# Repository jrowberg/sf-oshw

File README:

This repository holds various design files for hardware developed for SectorFej products and projects, such as the Bluegiga WT12 breakout boards.

For modules that have multiple versions published, it is usually desirable to use the most recent version unless you have a very specific reason not to. Duh, I know.

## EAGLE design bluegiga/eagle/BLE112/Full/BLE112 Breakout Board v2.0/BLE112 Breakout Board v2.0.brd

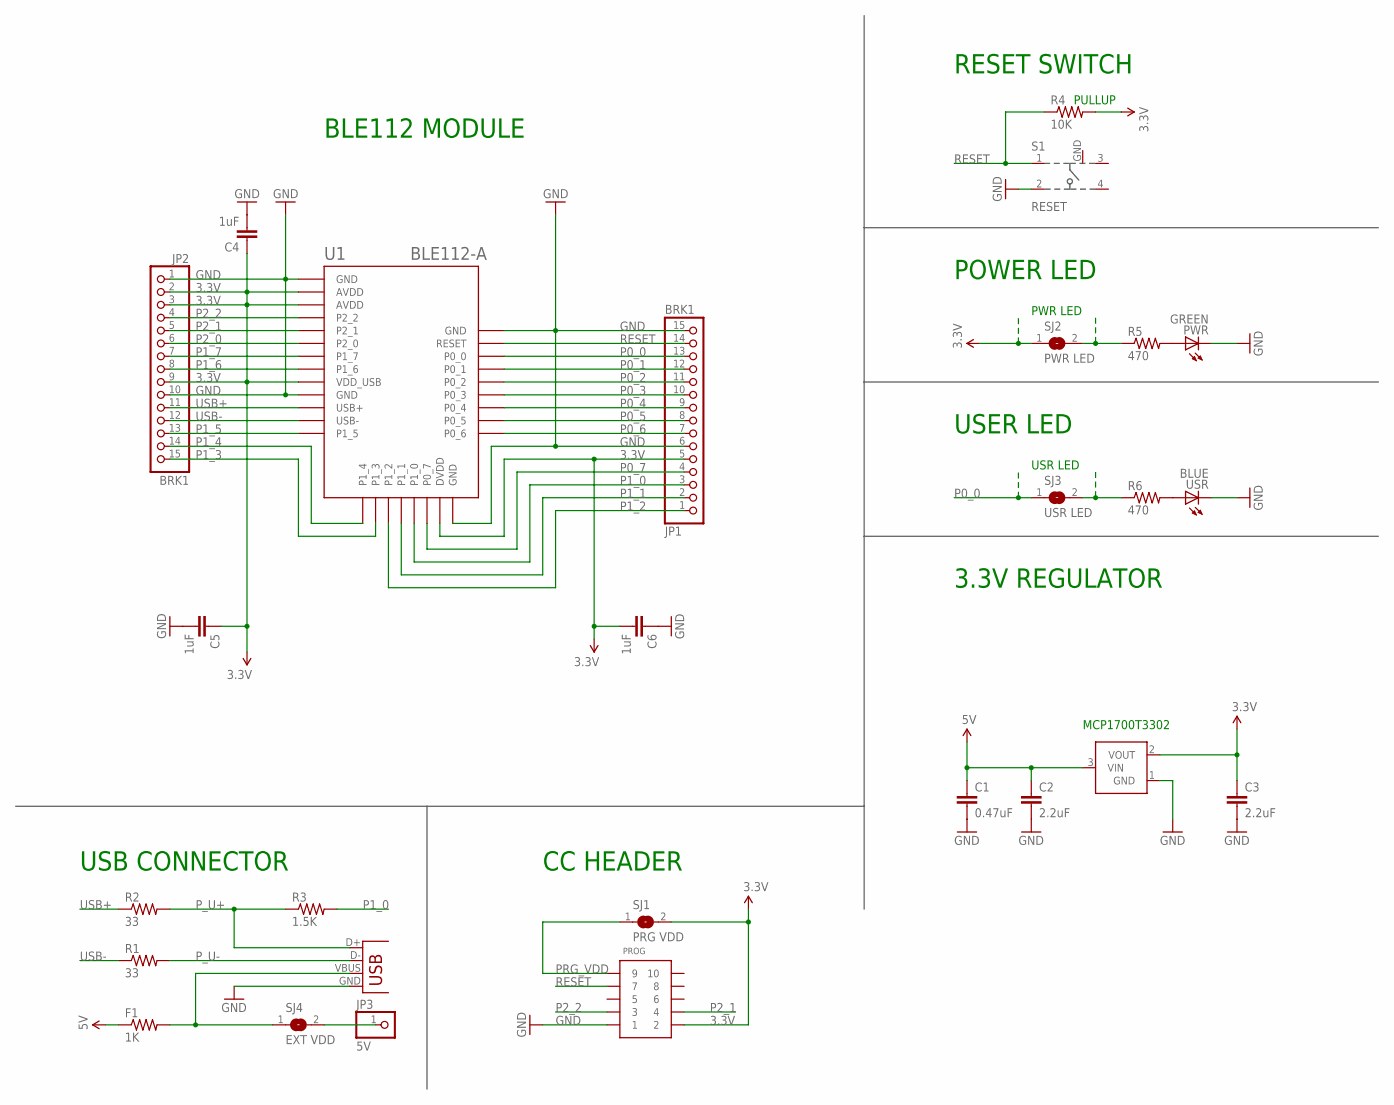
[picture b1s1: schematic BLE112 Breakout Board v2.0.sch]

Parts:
C1: 0.47uF; 0603-CAP
C2, C3: 2.2uF; 0603-CAP
C4, C5, C6: 1uF; 0603-CAP
F1: 1K; 0805
JP1, JP2: BRK1; 1X15
JP3: 5V; 1X01
PROG: CONN_5-2-FTSH-V; FTSH-105-DV
PWR: GREEN; CHIPLED_0805
R1, R2: 33; 0603-RES
R3: 1.5K; 0603-RES
R4: 10K; 0603-RES
R5, R6: 470; R0603
S1: RESET; 101-IG
SJ1: PRG VDD; SJ
SJ2: PWR LED; SJ
SJ3: USR LED; SJ
SJ4: EXT VDD; SJ
U1: BLE112-A
U2: MCP1700; SOT23-3
USB: USB-MICROB
USR: BLUE; CHIPLED_0805

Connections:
3.3V: C3.1, C4.1, C5.1, C6.2, JP1.5, JP2.2, JP2.3, JP2.9, PROG.2, R4.2, SJ1.2, SJ2.1, U1.AVDD1 (AVDD), U1.AVDD2 (AVDD), U1.DVDD, U1.VDD_USB, U2.2 (VOUT)
5V: C1.1, C2.1, F1.1, U2.3 (VIN)
GND: C1.2, C2.2, C3.2, C4.2, C5.2, C6.1, JP1.6, JP1.15, JP2.1, JP2.10, PROG.1, PWR.C, S1.2, S1.GND, U1.GND1 (GND), U1.GND2 (GND), U1.GND3 (GND), U1.GND4 (GND), U2.1 (GND), USB.GND, USR.C
unnamed: PWR.A, R5.2
unnamed: R5.1, SJ2.2
unnamed: R6.2, USR.A
unnamed: R6.1, SJ3.2
unnamed: JP3.1, SJ4.2
P0_0: JP1.13, SJ3.1, U1.P0_0
P0_1: JP1.12, U1.P0_1
P0_2: JP1.11, U1.P0_2
P0_3: JP1.10, U1.P0_3
P0_4: JP1.9, U1.P0_4
P0_5: JP1.8, U1.P0_5
P0_6: JP1.7, U1.P0_6
P0_7: JP1.4, U1.P0_7
P1_0: JP1.3, R3.2, U1.P1_0
P1_1: JP1.2, U1.P1_1
P1_2: JP1.1, U1.P1_2
P1_3: JP2.15, U1.P1_3
P1_4: JP2.14, U1.P1_4
P1_5: JP2.13, U1.P1_5
P1_6: JP2.8, U1.P1_6
P1_7: JP2.7, U1.P1_7
P2_0: JP2.6, U1.P2_0
P2_1: JP2.5, PROG.4, U1.P2_1
P2_2: JP2.4, PROG.3, U1.P2_2
PRG_VDD: PROG.9, SJ1.1
P_U+: R2.2, R3.1, USB.D+
P_U-: R1.2, USB.D-
RESET: JP1.14, PROG.7, R4.1, S1.1, U1.RESET
USB+: JP2.11, R2.1, U1.USB+
USB-: JP2.12, R1.1, U1.USB-
VBUS: F1.2, SJ4.1, USB.VBUS

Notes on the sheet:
PWR LED
USR LED
POWER LED
USER LED
USB CONNECTOR
CC HEADER
BLE112 MODULE
3.3V REGULATOR
RESET SWITCH
PULLUP
MCP1700T3302

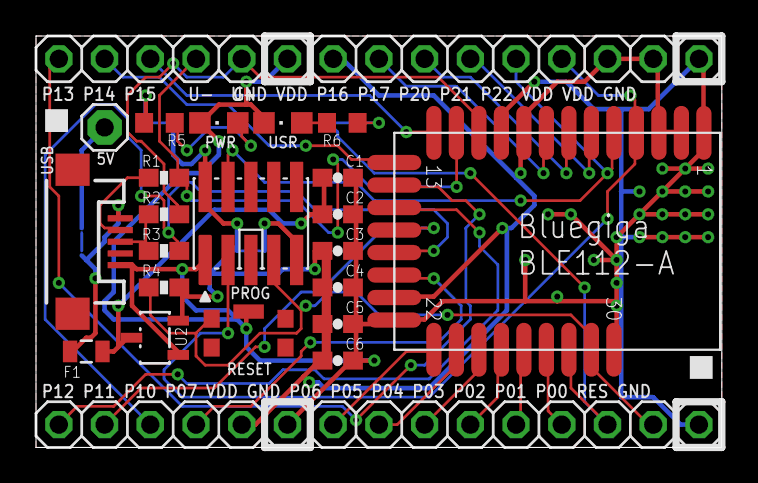
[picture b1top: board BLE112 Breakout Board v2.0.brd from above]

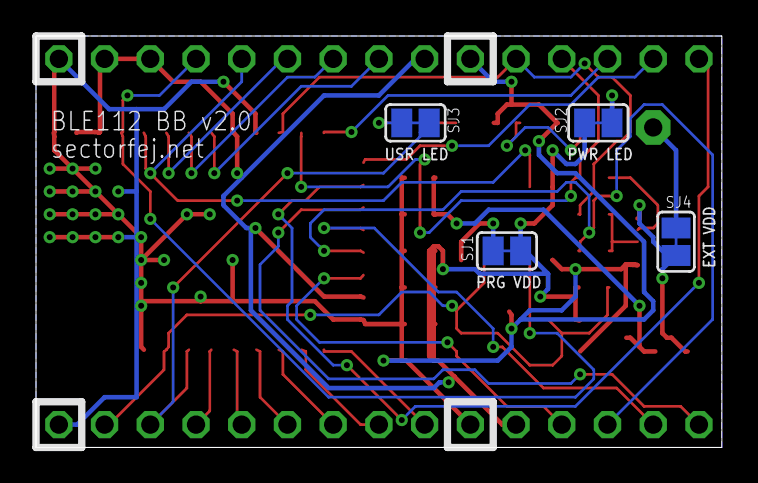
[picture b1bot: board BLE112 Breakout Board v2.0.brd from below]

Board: 2 copper layers, 38.1 x 22.9 mm, 27 parts (4 on the bottom side), 34 nets.

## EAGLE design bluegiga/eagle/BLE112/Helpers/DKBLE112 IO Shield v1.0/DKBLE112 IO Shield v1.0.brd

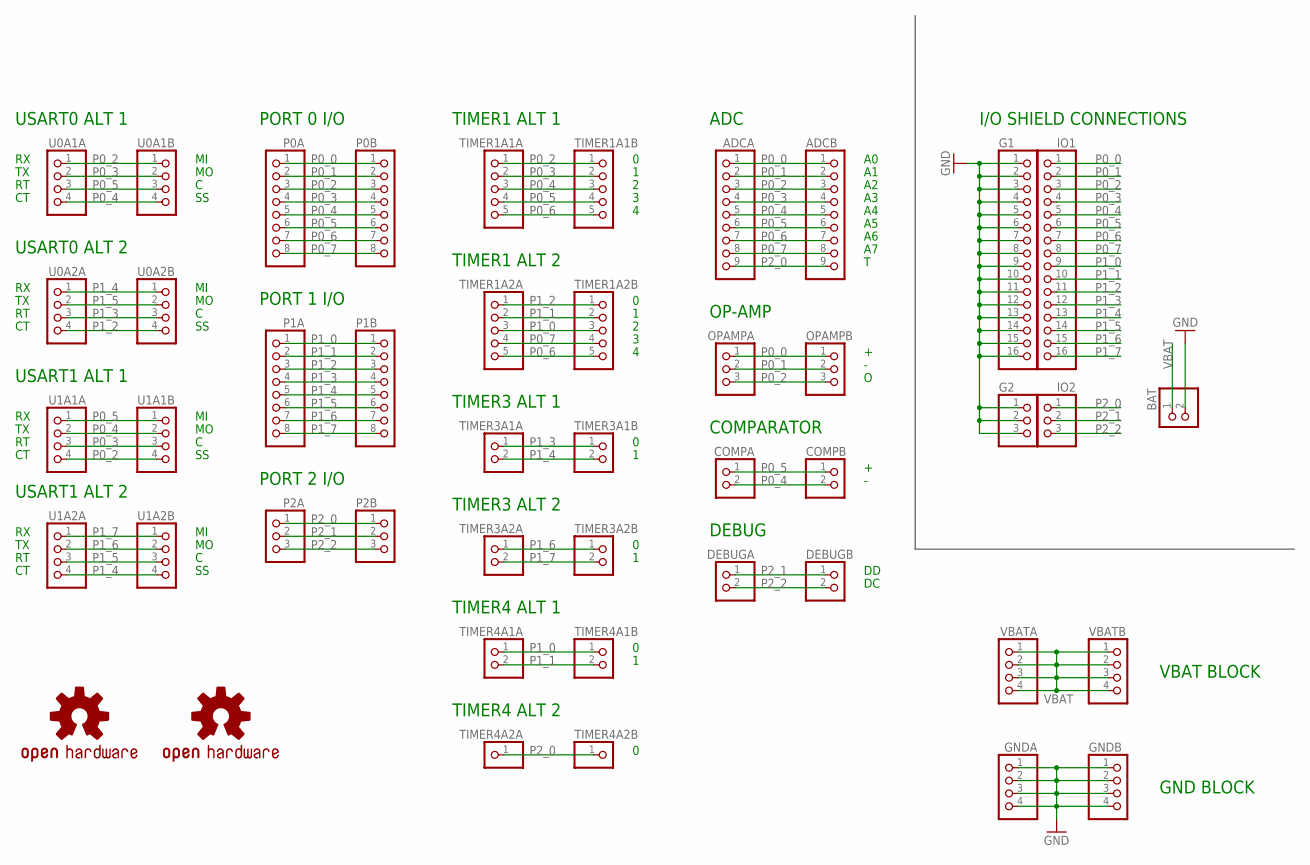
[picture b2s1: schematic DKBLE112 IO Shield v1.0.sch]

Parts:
ADCA: PINHD-1X9; 1X09
ADCB: PINHD-1X9; 1X09
BAT: PINHD-1X2; 1X02
COMPA: PINHD-1X2; 1X02
COMPB: PINHD-1X2; 1X02
DEBUGA: PINHD-1X2; 1X02
DEBUGB: PINHD-1X2; 1X02
G1: PINHD-1X16; 1X16
G2: PINHD-1X3; 1X03
GNDA: PINHD-1X4; 1X04
GNDB: PINHD-1X4; 1X04
IO1: PINHD-1X16; 1X16
IO2: PINHD-1X3; 1X03
OPAMPA: PINHD-1X3; 1X03
OPAMPB: PINHD-1X3; 1X03
P0A, P0B, P1A, P1B: PINHD-1X8; 1X08
P2A, P2B: PINHD-1X3; 1X03
TIMER1A1A, TIMER1A1B, TIMER1A2A, TIMER1A2B: PINHD-1X5; 1X05
TIMER3A1A, TIMER3A1B, TIMER3A2A, TIMER3A2B, TIMER4A1A, TIMER4A1B: PINHD-1X2; 1X02
TIMER4A2A, TIMER4A2B: PINHD-1X1; 1X01
U0A1A, U0A1B, U0A2A, U0A2B, U1A1A, U1A1B, U1A2A, U1A2B: PINHD-1X4; 1X04
U$1: OSHW-LOGOL; OSHW-LOGO-L
U$2: OSHW-LOGOM; OSHW-LOGO-M
VBATA: PINHD-1X4; 1X04
VBATB: PINHD-1X4; 1X04

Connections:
GND: BAT.2, G1.1, G1.2, G1.3, G1.4, G1.5, G1.6, G1.7, G1.8, G1.9, G1.10, G1.11, G1.12, G1.13, G1.14, G1.15, G1.16, G2.1, G2.2, G2.3, GNDA.1, GNDA.2, GNDA.3, GNDA.4, GNDB.1, GNDB.2, GNDB.3, GNDB.4
P0_0: ADCA.1, ADCB.1, IO1.1, OPAMPA.1, OPAMPB.1, P0A.1, P0B.1
P0_1: ADCA.2, ADCB.2, IO1.2, OPAMPA.2, OPAMPB.2, P0A.2, P0B.2
P0_2: ADCA.3, ADCB.3, IO1.3, OPAMPA.3, OPAMPB.3, P0A.3, P0B.3, TIMER1A1A.1, TIMER1A1B.1, U0A1A.1, U0A1B.1, U1A1A.4, U1A1B.4
P0_3: ADCA.4, ADCB.4, IO1.4, P0A.4, P0B.4, TIMER1A1A.2, TIMER1A1B.2, U0A1A.2, U0A1B.2, U1A1A.3, U1A1B.3
P0_4: ADCA.5, ADCB.5, COMPA.2, COMPB.2, IO1.5, P0A.5, P0B.5, TIMER1A1A.3, TIMER1A1B.3, U0A1A.4, U0A1B.4, U1A1A.2, U1A1B.2
P0_5: ADCA.6, ADCB.6, COMPA.1, COMPB.1, IO1.6, P0A.6, P0B.6, TIMER1A1A.4, TIMER1A1B.4, U0A1A.3, U0A1B.3, U1A1A.1, U1A1B.1
P0_6: ADCA.7, ADCB.7, IO1.7, P0A.7, P0B.7, TIMER1A1A.5, TIMER1A1B.5, TIMER1A2A.5, TIMER1A2B.5
P0_7: ADCA.8, ADCB.8, IO1.8, P0A.8, P0B.8, TIMER1A2A.4, TIMER1A2B.4
P1_0: IO1.9, P1A.1, P1B.1, TIMER1A2A.3, TIMER1A2B.3, TIMER4A1A.1, TIMER4A1B.1
P1_1: IO1.10, P1A.2, P1B.2, TIMER1A2A.2, TIMER1A2B.2, TIMER4A1A.2, TIMER4A1B.2
P1_2: IO1.11, P1A.3, P1B.3, TIMER1A2A.1, TIMER1A2B.1, U0A2A.4, U0A2B.4
P1_3: IO1.12, P1A.4, P1B.4, TIMER3A1A.1, TIMER3A1B.1, U0A2A.3, U0A2B.3
P1_4: IO1.13, P1A.5, P1B.5, TIMER3A1A.2, TIMER3A1B.2, U0A2A.1, U0A2B.1, U1A2A.4, U1A2B.4
P1_5: IO1.14, P1A.6, P1B.6, U0A2A.2, U0A2B.2, U1A2A.3, U1A2B.3
P1_6: IO1.15, P1A.7, P1B.7, TIMER3A2A.1, TIMER3A2B.1, U1A2A.2, U1A2B.2
P1_7: IO1.16, P1A.8, P1B.8, TIMER3A2A.2, TIMER3A2B.2, U1A2A.1, U1A2B.1
P2_0: ADCA.9, ADCB.9, IO2.1, P2A.1, P2B.1, TIMER4A2A.1, TIMER4A2B.1
P2_1: DEBUGA.1, DEBUGB.1, IO2.2, P2A.2, P2B.2
P2_2: DEBUGA.2, DEBUGB.2, IO2.3, P2A.3, P2B.3
VBAT: BAT.1, VBATA.1, VBATA.2, VBATA.3, VBATA.4, VBATB.1, VBATB.2, VBATB.3, VBATB.4

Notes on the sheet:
USART0 ALT 1
USART1 ALT 1
USART0 ALT 2
USART1 ALT 2
PORT 0 I/O
PORT 1 I/O
PORT 2 I/O
TIMER1 ALT 1
TIMER1 ALT 2
TIMER3 ALT 1
TIMER4 ALT 1
TIMER3 ALT 2
TIMER4 ALT 2
ADC
COMPARATOR
OP-AMP
I/O SHIELD CONNECTIONS
DEBUG
VBAT BLOCK
GND BLOCK

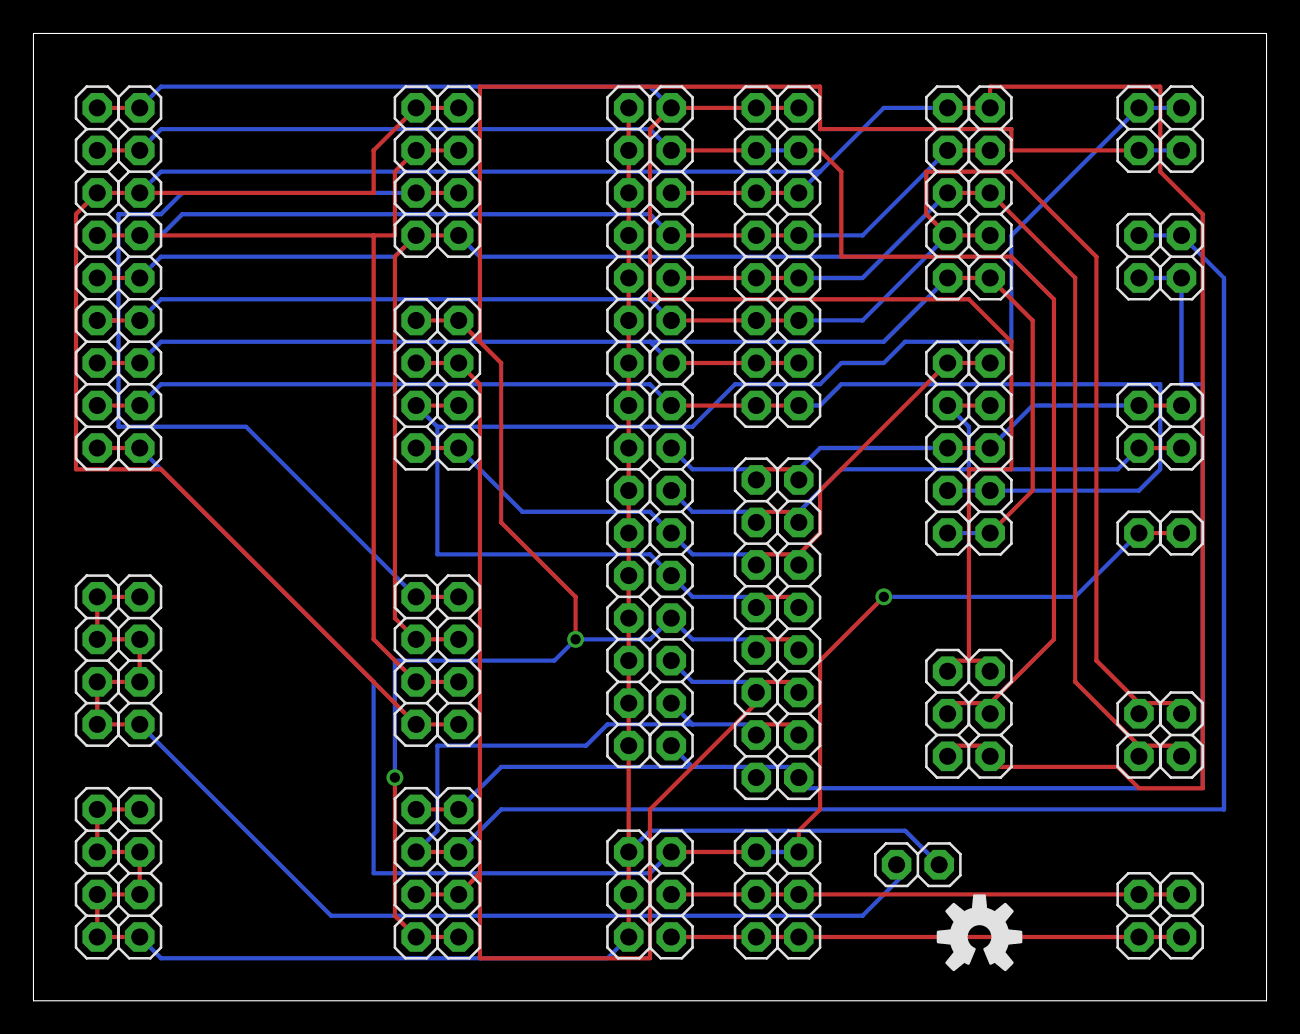
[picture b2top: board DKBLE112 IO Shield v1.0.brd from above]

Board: 2 copper layers, 73.7 x 57.8 mm, 45 parts (1 on the bottom side), 21 nets.

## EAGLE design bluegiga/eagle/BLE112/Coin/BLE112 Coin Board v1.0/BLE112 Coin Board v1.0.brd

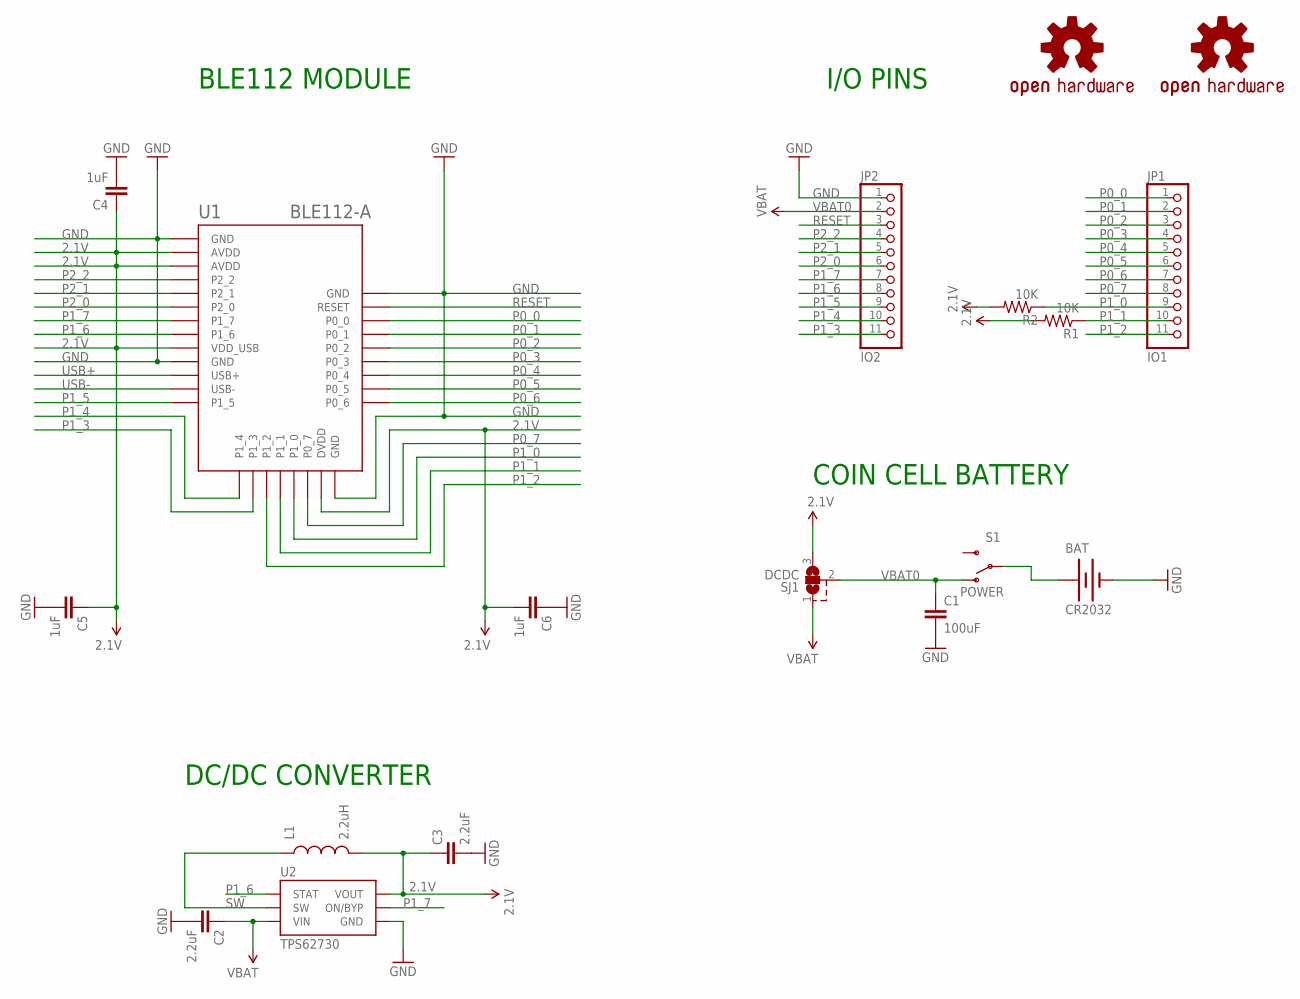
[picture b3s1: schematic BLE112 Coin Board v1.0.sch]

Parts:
BAT: CR2032; BATTCON_20MM_4LEGS
C1: 100uF; 0805
C2, C3: 2.2uF; 0603-CAP
C4, C5, C6: 1uF; 0603-CAP
JP1: IO1; 1X11
JP2: IO2; 1X11
L1: 2.2uH; 0603
R1, R2: 10K; 0603-RES
S1: POWER; SWITCH-SPST-SMD-A
SJ1: DCDC; SJ2-TRACE
U1: BLE112-A
U2: TPS62730
U$1, U$2: OSHW-LOGOS; OSHW-LOGO-S

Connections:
2.1V: C3.1, C4.1, C5.1, C6.2, L1.2, R1.2, R2.2, SJ1.3, U1.AVDD1 (AVDD), U1.AVDD2 (AVDD), U1.DVDD, U1.VDD_USB, U2.VOUT
GND: BAT.2 (-), C1.2, C2.2, C3.2, C4.2, C5.2, C6.1, JP2.1, U1.GND1 (GND), U1.GND2 (GND), U1.GND3 (GND), U1.GND4 (GND), U2.GND
unnamed: BAT.1 (+), S1.2
P0_0: JP1.1, U1.P0_0
P0_1: JP1.2, U1.P0_1
P0_2: JP1.3, U1.P0_2
P0_3: JP1.4, U1.P0_3
P0_4: JP1.5, U1.P0_4
P0_5: JP1.6, U1.P0_5
P0_6: JP1.7, U1.P0_6
P0_7: JP1.8, U1.P0_7
P1_0: JP1.9, R2.1, U1.P1_0
P1_1: JP1.10, R1.1, U1.P1_1
P1_2: JP1.11, U1.P1_2
P1_3: JP2.11, U1.P1_3
P1_4: JP2.10, U1.P1_4
P1_5: JP2.9, U1.P1_5
P1_6: JP2.8, U1.P1_6, U2.STAT
P1_7: JP2.7, U1.P1_7, U2.ON/BYP
P2_0: JP2.6, U1.P2_0
P2_1: JP2.5, U1.P2_1
P2_2: JP2.4, U1.P2_2
RESET: JP2.3, U1.RESET
SW: L1.1, U2.SW
USB+: U1.USB+
USB-: U1.USB-
VBAT: C2.1, SJ1.1, U2.VIN
VBAT0: C1.1, JP2.2, S1.1 (O), SJ1.2

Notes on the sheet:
BLE112 MODULE
I/O PINS
COIN CELL BATTERY
DC/DC CONVERTER

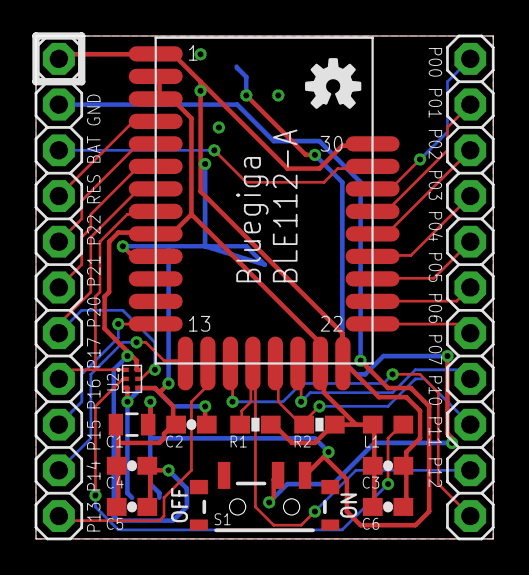
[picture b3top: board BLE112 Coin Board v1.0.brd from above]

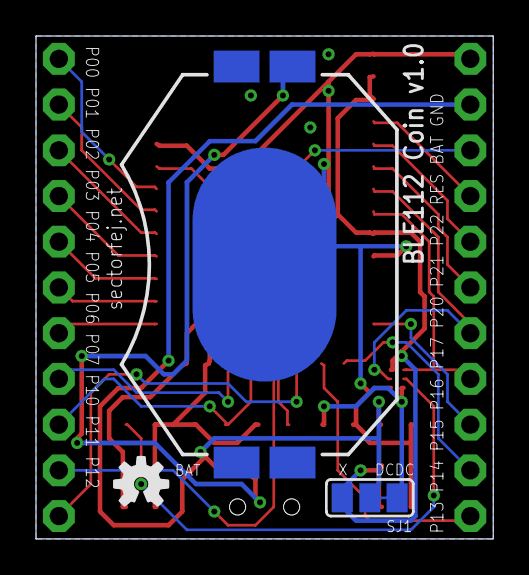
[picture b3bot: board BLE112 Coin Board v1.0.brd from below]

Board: 2 copper layers, 25.4 x 27.9 mm, 18 parts (3 on the bottom side), 26 nets.

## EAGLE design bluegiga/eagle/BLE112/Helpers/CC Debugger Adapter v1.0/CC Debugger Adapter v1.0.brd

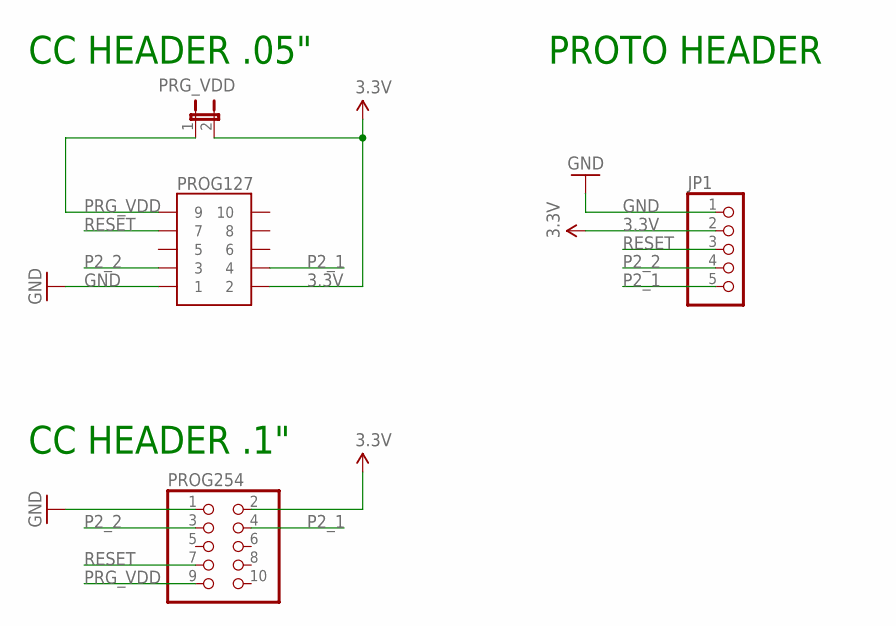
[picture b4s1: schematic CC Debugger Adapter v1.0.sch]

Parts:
JP1: PINHD-1X5; 1X05
PRG_VDD: JUMPER-2PTH; 1X02
PROG127: CONN_5-2-FTSH-V; FTSH-105-DV
PROG254: HEADER-2X5; 2X05

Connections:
3.3V: JP1.2, PRG_VDD.2, PROG127.2, PROG254.2
GND: JP1.1, PROG127.1, PROG254.1
P2_1: JP1.5, PROG127.4, PROG254.4
P2_2: JP1.4, PROG127.3, PROG254.3
PRG_VDD: PRG_VDD.1, PROG127.9, PROG254.9
RESET: JP1.3, PROG127.7, PROG254.7

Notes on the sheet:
CC HEADER .05"
CC HEADER .1"
PROTO HEADER

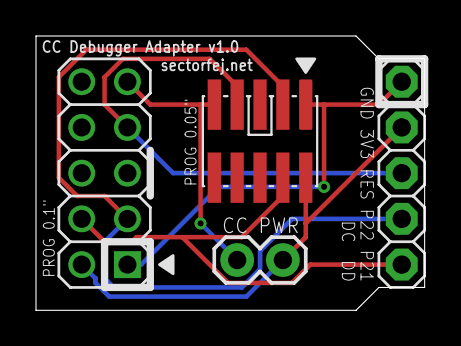
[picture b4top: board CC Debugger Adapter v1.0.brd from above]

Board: 2 copper layers, 21.6 x 15.2 mm, 4 parts (0 on the bottom side), 6 nets.

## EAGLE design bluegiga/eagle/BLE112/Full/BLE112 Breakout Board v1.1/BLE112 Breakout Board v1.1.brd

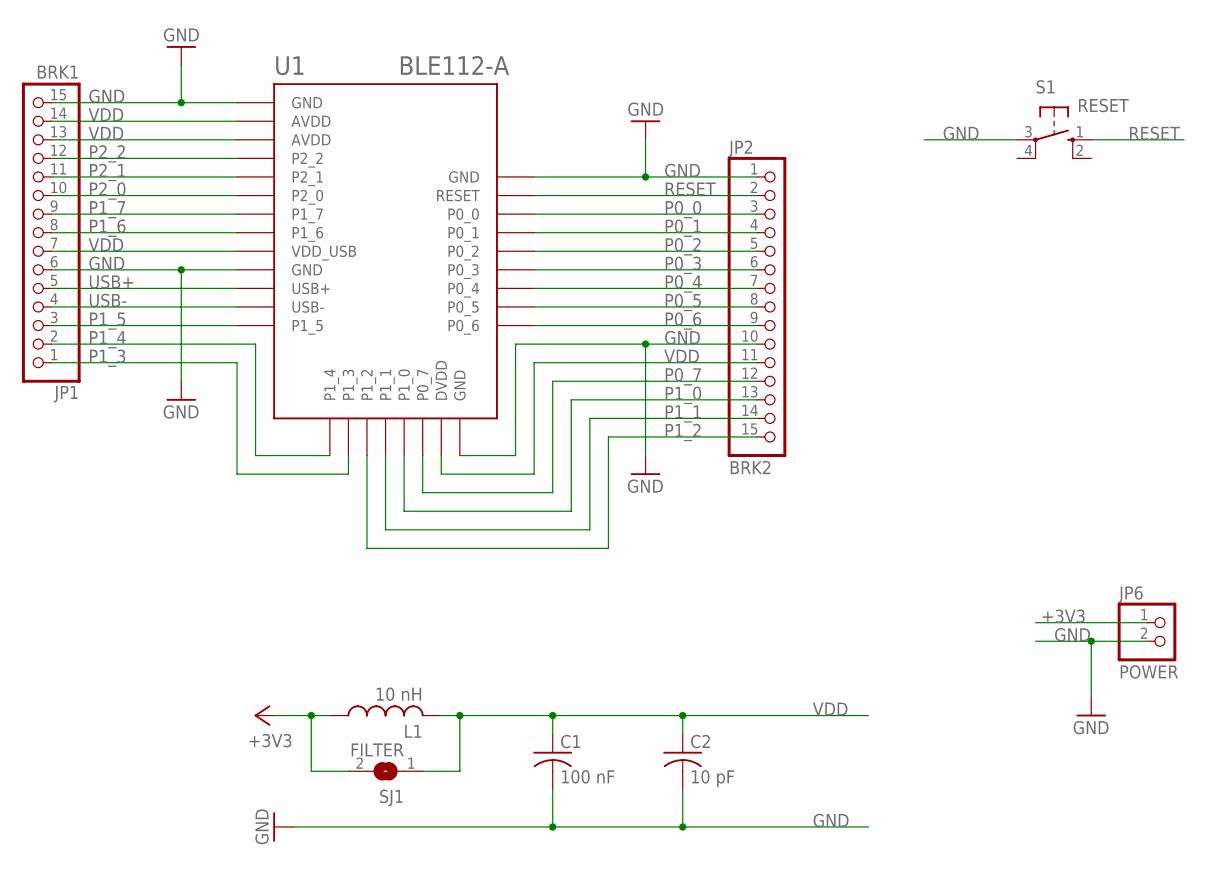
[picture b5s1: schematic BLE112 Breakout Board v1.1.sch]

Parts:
C1: 100 nF; C025-025X050
C2: 10 pF; C025-025X050
JP1: BRK1; 1X15
JP2: BRK2; 1X15
JP6: POWER; 1X02
L1: 10 nH; 0204/7
S1: RESET; B3F-10XX
SJ1: FILTER; SJ
U1: BLE112-A

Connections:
+3V3: JP6.1, L1.1, SJ1.2
GND: C1.2, C2.2, JP1.6, JP1.15, JP2.1, JP2.10, JP6.2, S1.3, U1.GND1 (GND), U1.GND2 (GND), U1.GND3 (GND), U1.GND4 (GND)
P0_0: JP2.3, U1.P0_0
P0_1: JP2.4, U1.P0_1
P0_2: JP2.5, U1.P0_2
P0_3: JP2.6, U1.P0_3
P0_4: JP2.7, U1.P0_4
P0_5: JP2.8, U1.P0_5
P0_6: JP2.9, U1.P0_6
P0_7: JP2.12, U1.P0_7
P1_0: JP2.13, U1.P1_0
P1_1: JP2.14, U1.P1_1
P1_2: JP2.15, U1.P1_2
P1_3: JP1.1, U1.P1_3
P1_4: JP1.2, U1.P1_4
P1_5: JP1.3, U1.P1_5
P1_6: JP1.8, U1.P1_6
P1_7: JP1.9, U1.P1_7
P2_0: JP1.10, U1.P2_0
P2_1: JP1.11, U1.P2_1
P2_2: JP1.12, U1.P2_2
RESET: JP2.2, S1.1 (S), U1.RESET
USB+: JP1.5, U1.USB+
USB-: JP1.4, U1.USB-
VDD: C1.1, C2.1, JP1.7, JP1.13, JP1.14, JP2.11, L1.2, SJ1.1, U1.AVDD1 (AVDD), U1.AVDD2 (AVDD), U1.DVDD, U1.VDD_USB

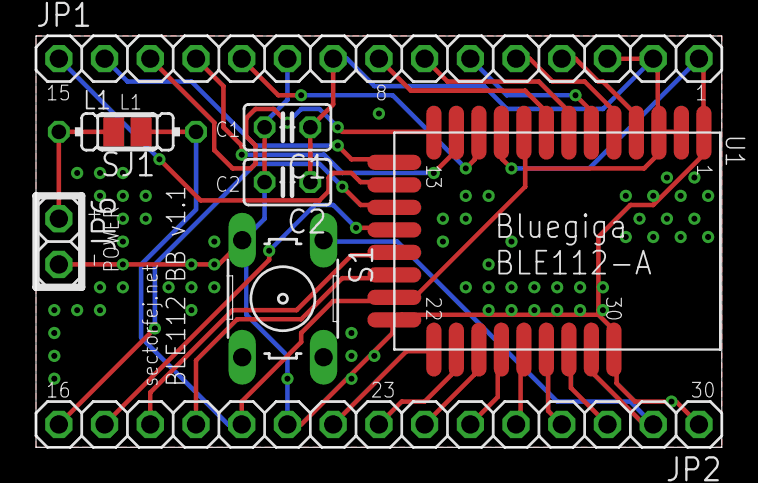
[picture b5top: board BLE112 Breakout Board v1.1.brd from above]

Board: 2 copper layers, 38.1 x 22.9 mm, 9 parts (0 on the bottom side), 25 nets.

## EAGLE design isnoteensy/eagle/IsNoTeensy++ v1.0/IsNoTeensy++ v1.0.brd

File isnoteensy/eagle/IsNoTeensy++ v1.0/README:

The AT90USB1286 (or its host-capable 1287 counterpart) is one of the most compact and comprehensively powerful AVR microcontrollers I have had the pleasure of using so far. If you're looking to integrate this MCU into one of your projects, the IsNoTeensy++ design is a perfect starting point. Details on the design process available here:

http://www.sectorfej.net/2012/02/24/isnoteensy-clone-schematic-and-pcb-for-at90usb1286-7-projects

Let me be extremely up-front about something: I am not trying to steal market share from Paul over at PJRC, the guy behind the real Teensy++. The IsNoTeensy++ is an almost perfect clone of the circuit and PCB layout, but it is not exactly the same thing as a real Teensy from PRJC for a few critical reasons:

- No Halfkay bootloader. You can't use the IsNoTeensy++ directly with Teensyduino or the Arduino IDE unless you manage to get a compatible bootloader on there yourself.

- You can't buy the IsNoTeensy++ anywhere. You have to build it yourself or have somebody else do it. With a 64-pin MLF IC and many 0402 SMDs onboard, this is going to be either difficult or expensive.

- The IsNoTeensy design comes AS-IS with absolutely no support or guarantees. You're on your own.

In contrast, if you buy a real Teensy++ from PJRC, you get a pre-built, tested board that integrates perfectly with Arduino software and has a devoted and very helpful guy behind it. On top of all this, the real Teensy has a very wide user base and proven track record. This is definitely worth the $24 it takes to get one from PJRC. If you want a Teensy, BUY A TEENSY:

http://www.pjrc.com/store/teensypp.html

Now that that's out of the way, if you're looking to integrate the AT90USB1286 (or USB-host-capable AT90USB1287) microcontroller into your design, this is a great way to get started.

Note that you should use Eagle 6.1 or later for full compatibility with the design. The USB connector uses a single pin connection to designate five pads on the connector package itself, and this is a new feature introduced in v6.

==================================================================================
All schematics, layouts, models, and images released under the CC-BY-SA-3 license.

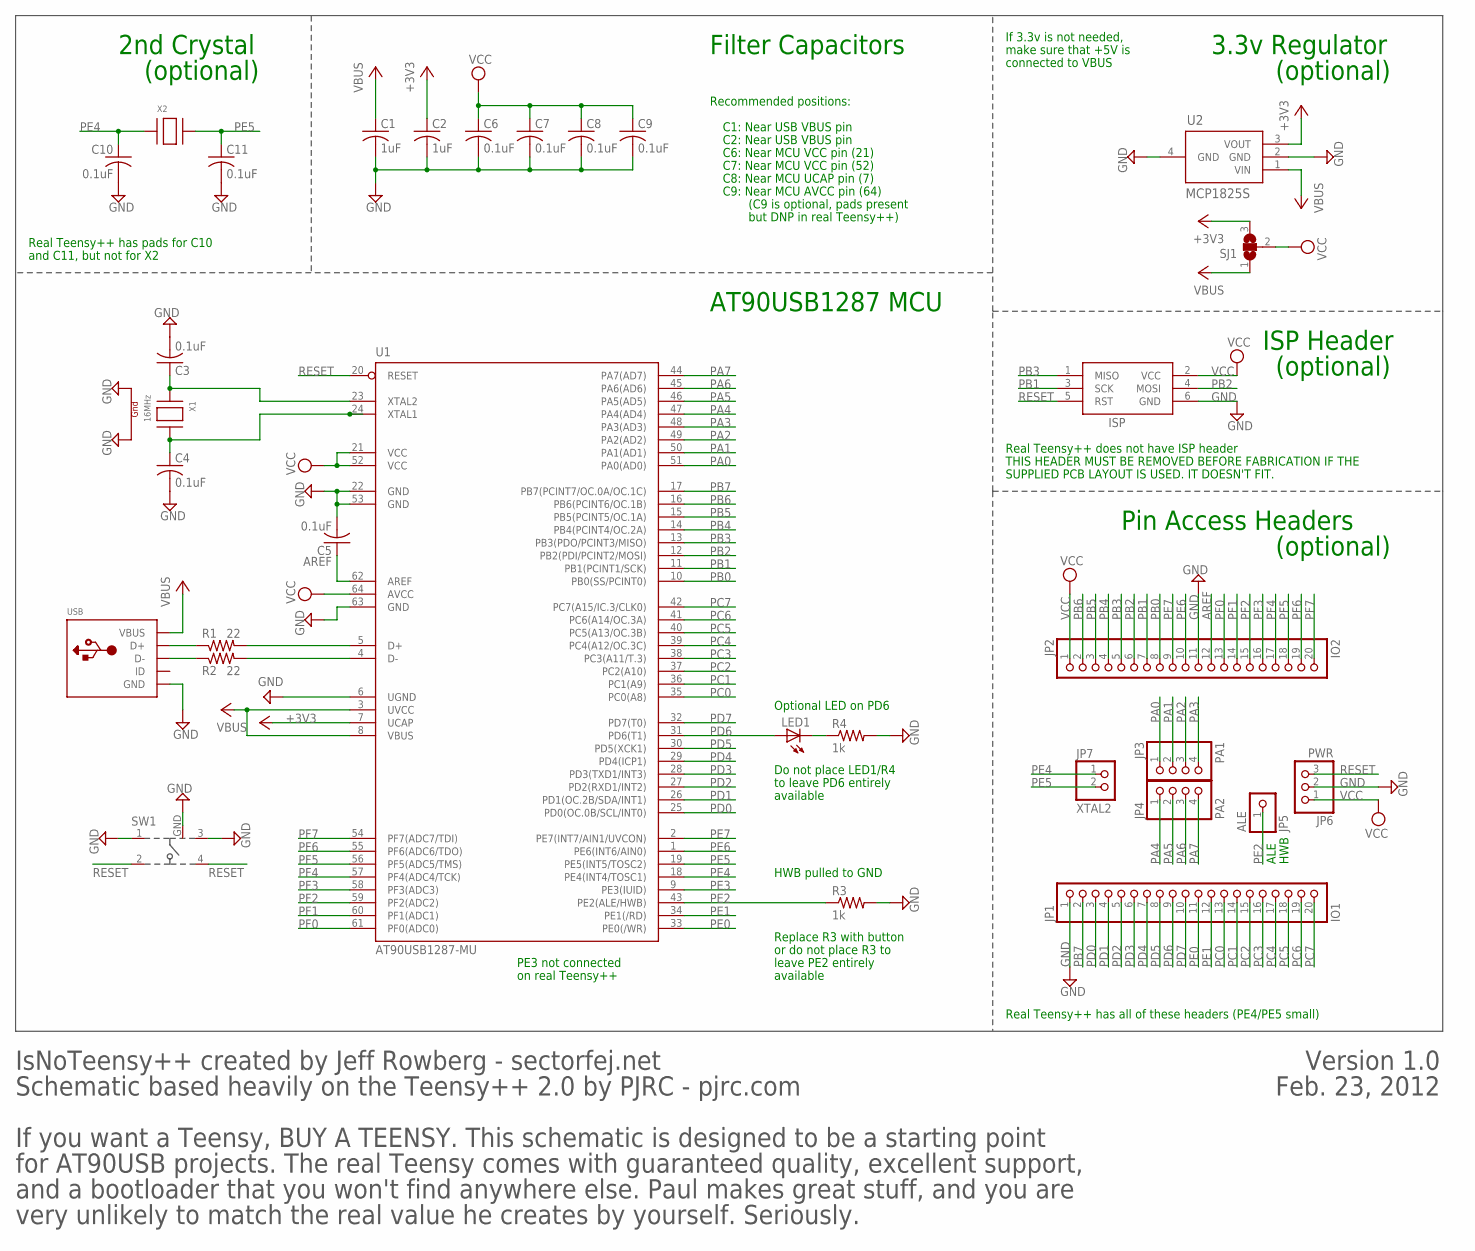
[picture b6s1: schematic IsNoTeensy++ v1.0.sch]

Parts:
C1, C2: 1uF; C0603
C3, C4, C5, C6, C7, C8: 0.1uF; C0402
C9, C10, C11: 0.1uF; C0805
ISP: AVRISP-6; AVRISP
JP1: IO1; 1X20
JP2: IO2; 1X20
JP3: PA1; 1X04
JP4: PA2; 1X04
JP5: ALE; 1X01
JP6: PWR; 1X03
JP7: XTAL2; 1X02
LED1: LEDCHIP-LED0603; CHIP-LED0603
R1, R2: 22; R0402
R3, R4: 1k; R0402
SJ1: SJ2W; SJ_2
SW1: 101-IG
U1: AT90USB1287-MU; MLF64
U2: MCP1825S; SOT223
USB: USBMINIB; USB-MINIB
X1: 16MHz; NX3225
X2: XTAL-3.2X1.5; XTAL3215

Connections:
+3V3: C2.1, SJ1.3, U1.7 (UCAP), U2.3 (VOUT)
AREF: C5.1, JP2.12, U1.62 (AREF)
D+: R1.2, U1.5 (D+)
D-: R2.2, U1.4 (D-)
GND: C1.2, C2.2, C3.2, C4.2, C5.2, C6.2, C7.2, C8.2, C9.2, C10.2, C11.2, ISP.6 (GND), JP1.1, JP2.11, JP6.2, R3.2, R4.2, SW1.1, SW1.3, SW1.GND, U1.6 (UGND), U1.22 (GND), U1.53 (GND), U1.63 (GND), U2.2 (GND), U2.4 (GND), USB.GND, USB.GND1 (GND), USB.GND2 (GND), USB.GND3 (GND), USB.GND4 (GND), X1.2 (G1), X1.4 (G2)
unnamed: LED1.C, R4.1
unnamed: R1.1, USB.D+
unnamed: R2.1, USB.D-
unnamed: C4.1, U1.24 (XTAL1), X1.3 (X2)
unnamed: C3.1, U1.23 (XTAL2), X1.1 (X1)
PA0: JP3.1, U1.51 (PA0(AD0))
PA1: JP3.2, U1.50 (PA1(AD1))
PA2: JP3.3, U1.49 (PA2(AD2))
PA3: JP3.4, U1.48 (PA3(AD3))
PA4: JP4.1, U1.47 (PA4(AD4))
PA5: JP4.2, U1.46 (PA5(AD5))
PA6: JP4.3, U1.45 (PA6(AD6))
PA7: JP4.4, U1.44 (PA7(AD7))
PB0: JP2.8, U1.10 (PB0(SS/PCINT0))
PB1: ISP.3 (SCK), JP2.7, U1.11 (PB1(PCINT1/SCK))
PB2: ISP.4 (MOSI), JP2.6, U1.12 (PB2(PDI/PCINT2/MOSI))
PB3: ISP.1 (MISO), JP2.5, U1.13 (PB3(PDO/PCINT3/MISO))
PB4: JP2.4, U1.14 (PB4(PCINT4/OC.2A))
PB5: JP2.3, U1.15 (PB5(PCINT5/OC.1A))
PB6: JP2.2, U1.16 (PB6(PCINT6/OC.1B))
PB7: JP1.2, U1.17 (PB7(PCINT7/OC.0A/OC.1C))
PC0: JP1.13, U1.35 (PC0(A8))
PC1: JP1.14, U1.36 (PC1(A9))
PC2: JP1.15, U1.37 (PC2(A10))
PC3: JP1.16, U1.38 (PC3(A11/T.3))
PC4: JP1.17, U1.39 (PC4(A12/OC.3C))
PC5: JP1.18, U1.40 (PC5(A13/OC.3B))
PC6: JP1.19, U1.41 (PC6(A14/OC.3A))
PC7: JP1.20, U1.42 (PC7(A15/IC.3/CLK0))
PD0: JP1.3, U1.25 (PD0(OC.0B/SCL/INT0))
PD1: JP1.4, U1.26 (PD1(OC.2B/SDA/INT1))
PD2: JP1.5, U1.27 (PD2(RXD1/INT2))
PD3: JP1.6, U1.28 (PD3(TXD1/INT3))
PD4: JP1.7, U1.29 (PD4(ICP1))
PD5: JP1.8, U1.30 (PD5(XCK1))
PD6: JP1.9, LED1.A, U1.31 (PD6(T1))
PD7: JP1.10, U1.32 (PD7(T0))
PE0: JP1.11, U1.33 (PE0(/WR))
PE1: JP1.12, U1.34 (PE1(/RD))
PE2: JP5.1, R3.1, U1.43 (PE2(ALE/HWB))
PE3: U1.9 (PE3(IUID))
PE4: C10.1, JP7.1, U1.18 (PE4(INT4/TOSC1)), X2.P$1
PE5: C11.1, JP7.2, U1.19 (PE5(INT5/TOSC2)), X2.P$2
PE6: JP2.10, U1.1 (PE6(INT6/AIN0))
PE7: JP2.9, U1.2 (PE7(INT7/AIN1/UVCON))
PF0: JP2.13, U1.61 (PF0(ADC0))
PF1: JP2.14, U1.60 (PF1(ADC1))
PF2: JP2.15, U1.59 (PF2(ADC2))
PF3: JP2.16, U1.58 (PF3(ADC3))
PF4: JP2.17, U1.57 (PF4(ADC4/TCK))
PF5: JP2.18, U1.56 (PF5(ADC5/TMS))
PF6: JP2.19, U1.55 (PF6(ADC6/TDO))
PF7: JP2.20, U1.54 (PF7(ADC7/TDI))
RESET: ISP.5 (RST), JP6.3, SW1.2, SW1.4, U1.20 (RESET)
VBUS: C1.1, SJ1.1, U1.3 (UVCC), U1.8 (VBUS), U2.1 (VIN), USB.VBUS
VCC: C6.1, C7.1, C8.1, C9.1, ISP.2 (VCC), JP2.1, JP6.1, SJ1.2, U1.21 (VCC), U1.52 (VCC), U1.64 (AVCC)

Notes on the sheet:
ALE
3.3v Regulator
Pin Access Headers
HWB
AT90USB1287 MCU
HWB pulled to GND
Optional LED on PD6
Do not place LED1/R4
to leave PD6 entirely
available
Replace R3 with button
or do not place R3 to
leave PE2 entirely
If 3.3v is not needed,
connected to VBUS
Filter Capacitors
2nd Crystal
(optional)
Real Teensy++ has pads for C10
and C11, but not for X2
Recommended positions:
C1: Near USB VBUS pin
C2: Near USB VBUS pin
C6: Near MCU VCC pin (21)
C7: Near MCU VCC pin (52)
C8: Near MCU UCAP pin (7)
C9: Near MCU AVCC pin (64)
ISP Header
Real Teensy++ does not have ISP header
make sure that +5V is
Real Teensy++ has all of these headers (PE4/PE5 small)
(C9 is optional, pads present
but DNP in real Teensy++)
PE3 not connected
on real Teensy++
Schematic based heavily on the Teensy++ 2.0 by PJRC - pjrc.com
If you want a Teensy, BUY A TEENSY. This schematic is designed to be a starting point
for AT90USB projects. The real Teensy comes with guaranteed quality, excellent support,
and a bootloader that you won't find anywhere else. Paul makes great stuff, and you are
very unlikely to match the real value he creates by yourself. Seriously.

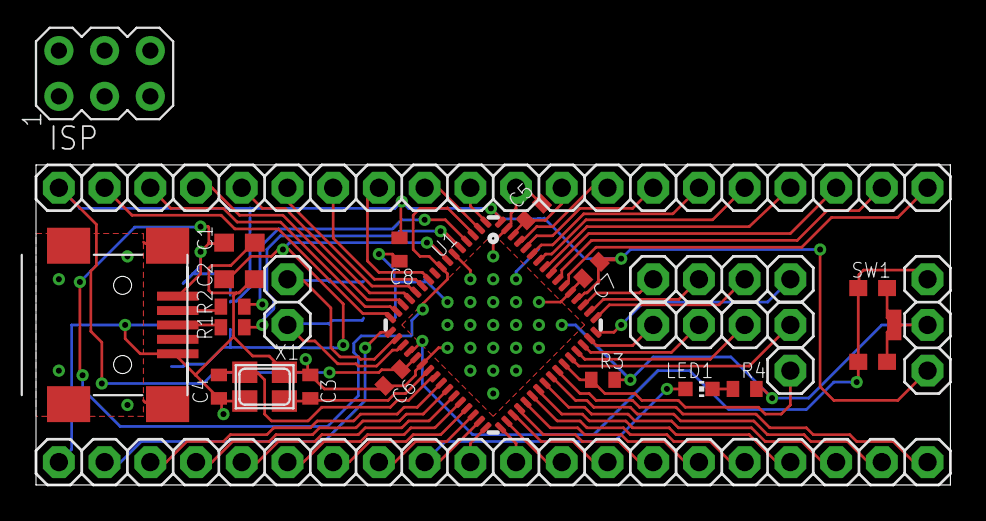
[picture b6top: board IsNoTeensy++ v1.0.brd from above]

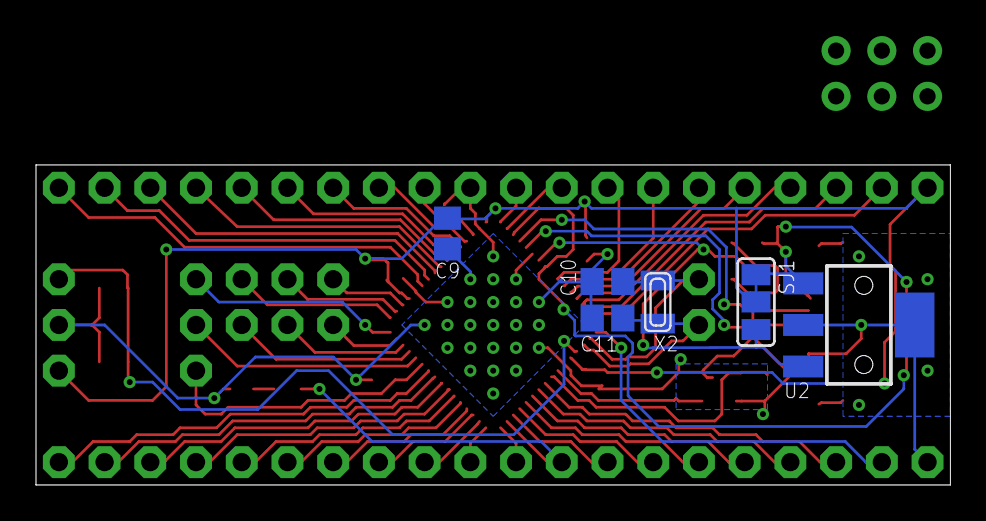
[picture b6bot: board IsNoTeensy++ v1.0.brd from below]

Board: 2 copper layers, 50.8 x 17.8 mm, 31 parts (6 on the bottom side), 60 nets.

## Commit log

2011-11-26 Create sf-oshw repository
2011-11-26 Add current Bluegiga library and projects
2012-02-24 Added IsNoTeensy++ v1.0 design files
2012-02-25 Updated README for IsNoTeensy++ v1.0
2012-02-25 Remove IsNoTeensy++ project for the moment
2013-01-01 Adding newest BLE112 board designs and helper/adapter boards
2013-02-02 Fix BLE112 v2.0 trial run PCB error
2013-02-27 Add BLE113-A, note active-low RESET pin on BLE112 parts, combine GND/AVDD pins on BLE112 module and update schematic symbol
2013-04-25 Add schematic/PCB PDFs for BLE112 v1.0 + v1.1
2013-09-27 Add WF121, other minor adjustments
2014-01-04 Significant update to Bluegiga Eagle library - all available Bluegiga modules now present, including BT111-A and WF111-A/E. All packages, symbols, and parts updated for consistency.
2014-01-06 Small updates to WT21 symbols for consistency
2014-08-03 Add BLE121LR-A module to sf-bluegiga Eagle library
2015-09-02 Added BGM111-A module, with organized and visual symbols.
2016-12-05 Corrected positions of PF0-PF7 pins in schematic symbol for BGM111-A

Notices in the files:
parts and their libraries:
SparkFun: Licensing: CC v3.0 Share-Alike You are welcome to use this library for commercial purposes.
